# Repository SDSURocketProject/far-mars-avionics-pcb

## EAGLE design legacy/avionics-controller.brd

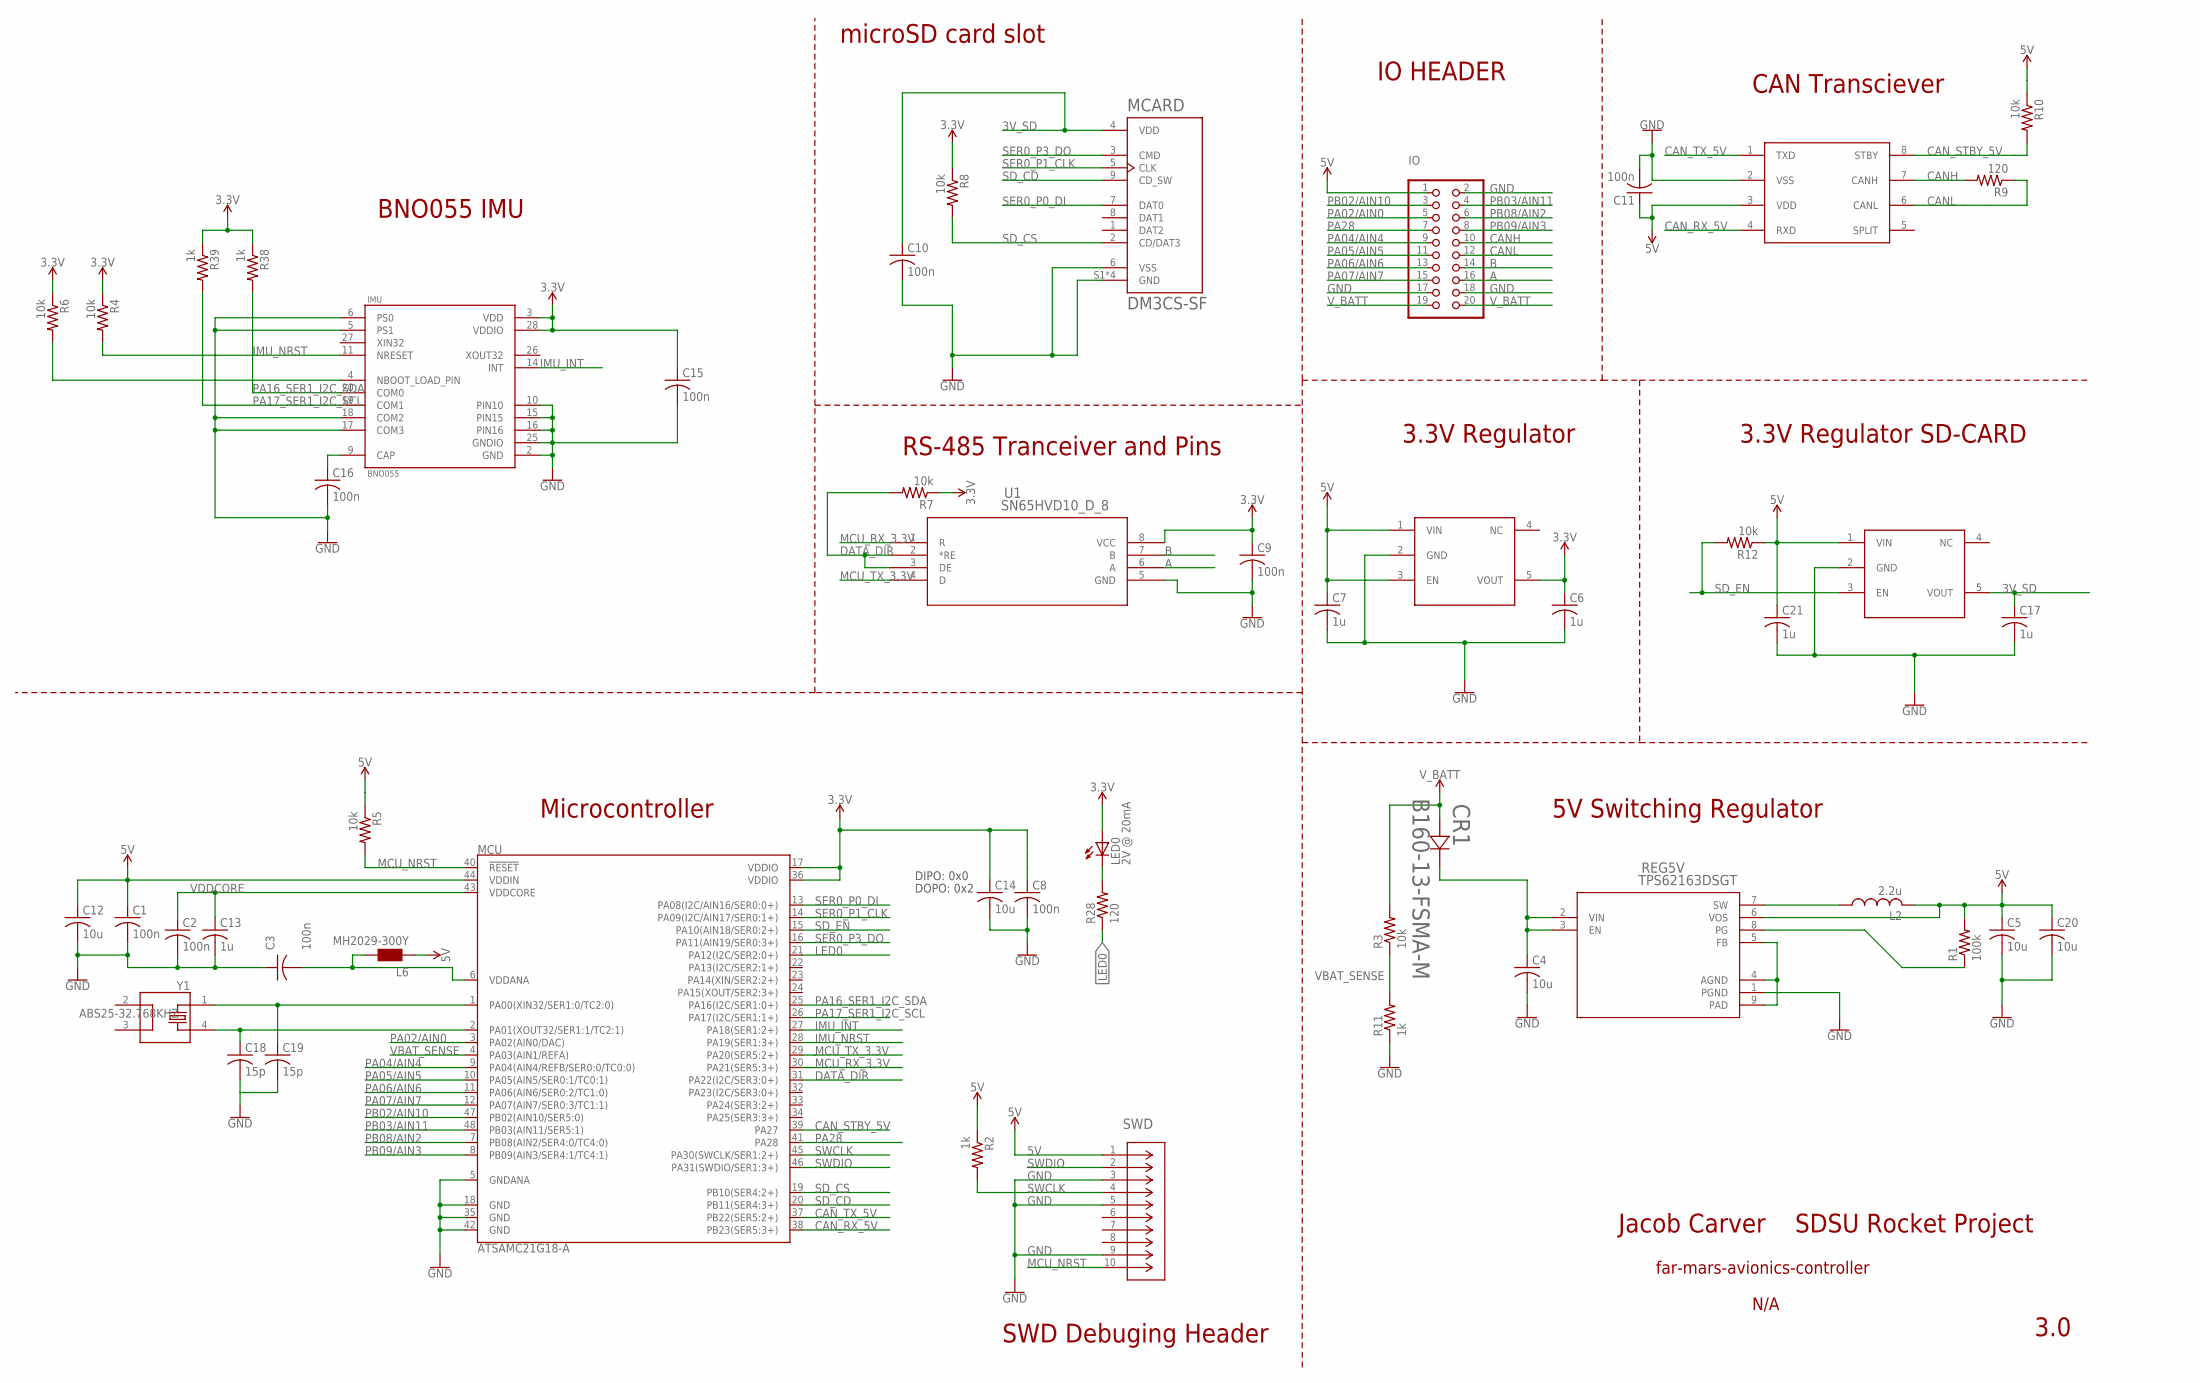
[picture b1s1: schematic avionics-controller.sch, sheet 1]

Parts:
3VREG, 3VREG-SD: 3.3VREGULATOR; SOT95P280X110-5
C1, C2, C3, C8, C9, C10, C11, C15, C16: 100n; C0402
C4, C5, C12, C14, C20: 10u; C0603
C6, C7, C13, C17, C21: 1u; C0402
C18, C19: 15p; C0402
CAN: MCP2561T-E8SOIC; SOIC127P600X175-8
CR1: B160-13-FSMA-M; SMA-M
IMU: BNO055; LGA28R50P4X10_380X520X100
IO: PINHD-2X10/90; 2X10/90
L2: 2.2u; L2012C
L6: MH2029-300Y; 0805
LED0: 2V @ 20mA; CHIPLED_0603
MCARD: DM3CS-SF; HRS_DM3CS-SF
MCU: ATSAMC21G18-A; TQFP-48
R1: 100k; R0402
R2, R11, R38, R39: 1k; R0402
R3, R4, R5, R6, R7, R8, R10, R12: 10k; R0402
R9, R28: 120; R0402
REG5V: TPS62163DSGT; DSG8_1P6X0P9
SWD: DEBUG-HEADER; CONN_MINITEK_2X5_HDR
U1: SN65HVD10_D_8; D8
Y1: ABS25-32.768KHZ; ABS25-32.768KHZ-6-T

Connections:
3.3V: 3VREG.5 (VOUT), C6.1, C8.1, C9.1, C14.1, C15.1, IMU.3 (VDD), IMU.28 (VDDIO), LED0.A, MCU.17 (VDDIO), MCU.36 (VDDIO), R4.1, R6.1, R7.1, R8.1, R38.1, R39.1, U1.8 (VCC)
3V_SD: 3VREG-SD.5 (VOUT), C10.1, C17.1, MCARD.4 (VDD)
5V: 3VREG.1 (VIN), 3VREG.3 (EN), 3VREG-SD.1 (VIN), C1.1, C5.1, C7.1, C11.1, C12.1, C20.1, C21.1, CAN.3 (VDD), IO.1, L2.2, L6.1, MCU.44 (VDDIN), R1.2, R2.1, R5.1, R10.1, R12.1, REG5V.6 (VOS), SWD.1
A: IO.16, U1.6 (A)
B: IO.14, U1.7 (B)
CANH: CAN.7 (CANH), IO.10, R9.2
CANL: CAN.6 (CANL), IO.12, R9.1
CAN_RX_5V: CAN.4 (RXD), MCU.38 (PB23(SER5:3+))
CAN_STBY_5V: CAN.8 (STBY), MCU.39 (PA27), R10.2
CAN_TX_5V: CAN.1 (TXD), MCU.37 (PB22(SER5:2+))
DATA_DIR: MCU.31 (PA22(I2C/SER3:0+)), R7.2, U1.2 (*RE), U1.3 (DE)
GND: 3VREG.2 (GND), 3VREG-SD.2 (GND), C1.2, C2.2, C3.1, C4.2, C5.2, C6.2, C7.2, C8.2, C9.2, C10.2, C11.2, C12.2, C13.2, C14.2, C15.2, C16.2, C17.2, C18.2, C19.2, C20.2, C21.2, CAN.2 (VSS), IMU.2 (GND), IMU.5 (PS1), IMU.6 (PS0), IMU.10 (PIN10), IMU.15 (PIN15), IMU.16 (PIN16), IMU.17 (COM3), IMU.18 (COM2), IMU.25 (GNDIO), IO.2, IO.17, IO.18, MCARD.6 (VSS), MCARD.S1 (GND), MCARD.S2 (GND), MCARD.S3 (GND), MCARD.S5 (GND), MCU.5 (GNDANA), MCU.18 (GND), MCU.35 (GND), MCU.42 (GND), R11.1, REG5V.1 (PGND), SWD.3, SWD.5, SWD.9, U1.5 (GND)
IMU_INT: IMU.14 (INT), MCU.27 (PA18(SER1:2+))
IMU_NRST: IMU.11 (NRESET), MCU.28 (PA19(SER1:3+)), R4.2
LED0: MCU.21 (PA12(I2C/SER2:0+)), R28.1
MCU_NRST: MCU.40 (!RESET!), R5.2, SWD.10
MCU_RX_3.3V: MCU.30 (PA21(SER5:3+)), U1.1 (R)
MCU_TX_3.3V: MCU.29 (PA20(SER5:2+)), U1.4 (D)
unnamed: R1.1, REG5V.8 (PG)
unnamed: C3.2, L6.2, MCU.6 (VDDANA)
unnamed: L2.1, REG5V.7 (SW)
unnamed: REG5V.4 (AGND), REG5V.5 (FB), REG5V.9 (PAD)
unnamed: C4.1, CR1.1 (12), REG5V.2 (VIN), REG5V.3 (EN)
unnamed: C19.1, MCU.1 (PA00(XIN32/SER1:0/TC2:0)), Y1.1
unnamed: C18.1, MCU.2 (PA01(XOUT32/SER1:1/TC2:1)), Y1.4
unnamed: C16.1, IMU.9 (CAP)
unnamed: IMU.4 (NBOOT_LOAD_PIN), R6.2
unnamed: LED0.C, R28.2
PA02/AIN0: IO.5, MCU.3 (PA02(AIN0/DAC))
PA04/AIN4: IO.9, MCU.9 (PA04(AIN4/REFB/SER0:0/TC0:0))
PA05/AIN5: IO.11, MCU.10 (PA05(AIN5/SER0:1/TC0:1))
PA06/AIN6: IO.13, MCU.11 (PA06(AIN6/SER0:2/TC1:0))
PA07/AIN7: IO.15, MCU.12 (PA07(AIN7/SER0:3/TC1:1))
PA16_SER1_I2C_SDA: IMU.20 (COM0), MCU.25 (PA16(I2C/SER1:0+)), R38.2
PA17_SER1_I2C_SCL: IMU.19 (COM1), MCU.26 (PA17(I2C/SER1:1+)), R39.2
PA28: IO.7, MCU.41 (PA28)
PB02/AIN10: IO.3, MCU.47 (PB02(AIN10/SER5:0))
PB03/AIN11: IO.4, MCU.48 (PB03(AIN11/SER5:1))
PB08/AIN2: IO.6, MCU.7 (PB08(AIN2/SER4:0/TC4:0))
PB09/AIN3: IO.8, MCU.8 (PB09(AIN3/SER4:1/TC4:1))
SD_CD: MCARD.9 (CD_SW), MCU.20 (PB11(SER4:3+))
SD_CS: MCARD.2 (CD/DAT3), MCU.19 (PB10(SER4:2+)), R8.2
SD_EN: 3VREG-SD.3 (EN), MCU.15 (PA10(AIN18/SER0:2+)), R12.2
SER0_P0_DI: MCARD.7 (DAT0), MCU.13 (PA08(I2C/AIN16/SER0:0+))
SER0_P1_CLK: MCARD.5 (CLK), MCU.14 (PA09(I2C/AIN17/SER0:1+))
SER0_P3_DO: MCARD.3 (CMD), MCU.16 (PA11(AIN19/SER0:3+))
SWCLK: MCU.45 (PA30(SWCLK/SER1:2+)), R2.2, SWD.4
SWDIO: MCU.46 (PA31(SWDIO/SER1:3+)), SWD.2
VBAT_SENSE: MCU.4 (PA03(AIN1/REFA)), R3.1, R11.2
VDDCORE: C2.1, C13.1, MCU.43 (VDDCORE)
V_BATT: CR1.2 (21), IO.19, IO.20, R3.2

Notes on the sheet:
DIPO: 0x0
DOPO: 0x2
RS-485 Tranceiver and Pins
SWD Debuging Header
microSD card slot
IO HEADER
3.3V Regulator
CAN Transciever
5V Switching Regulator
Microcontroller
BNO055 IMU
3.3V Regulator SD-CARD
3.0
Jacob Carver SDSU Rocket Project
N/A
far-mars-avionics-controller

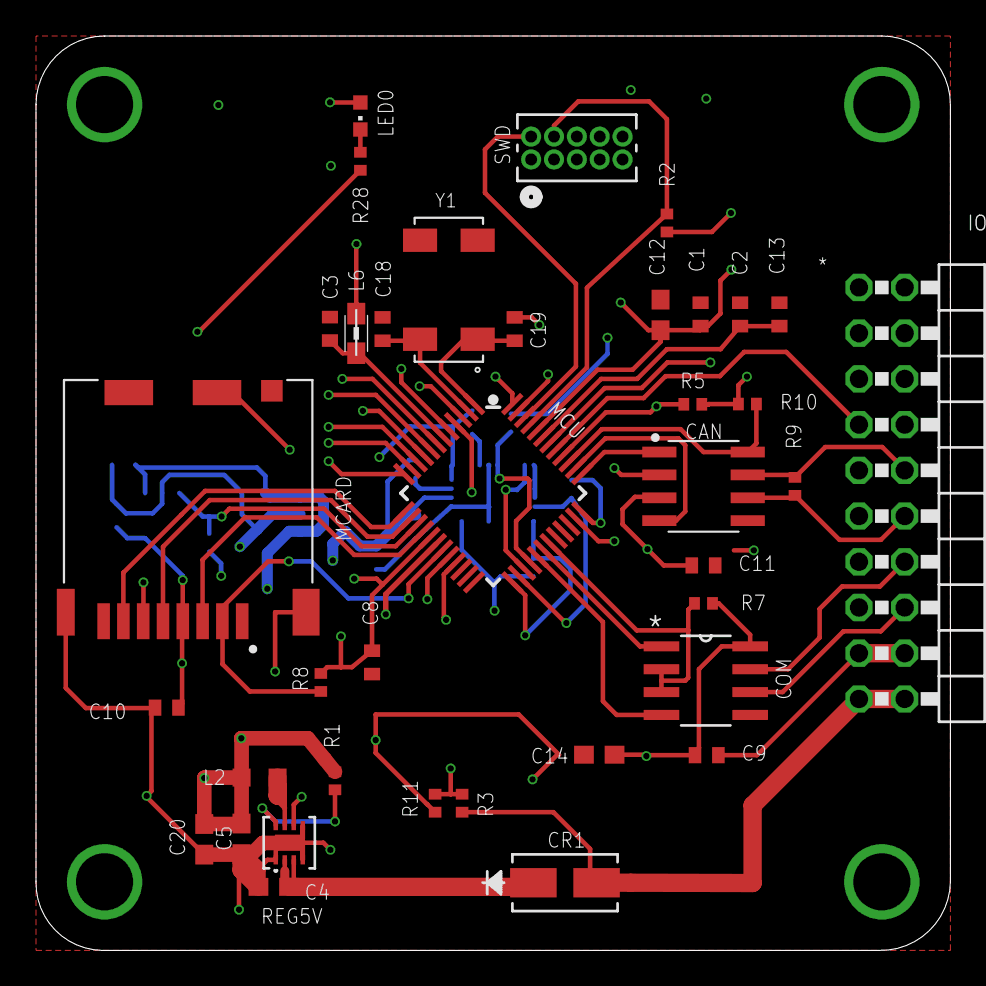
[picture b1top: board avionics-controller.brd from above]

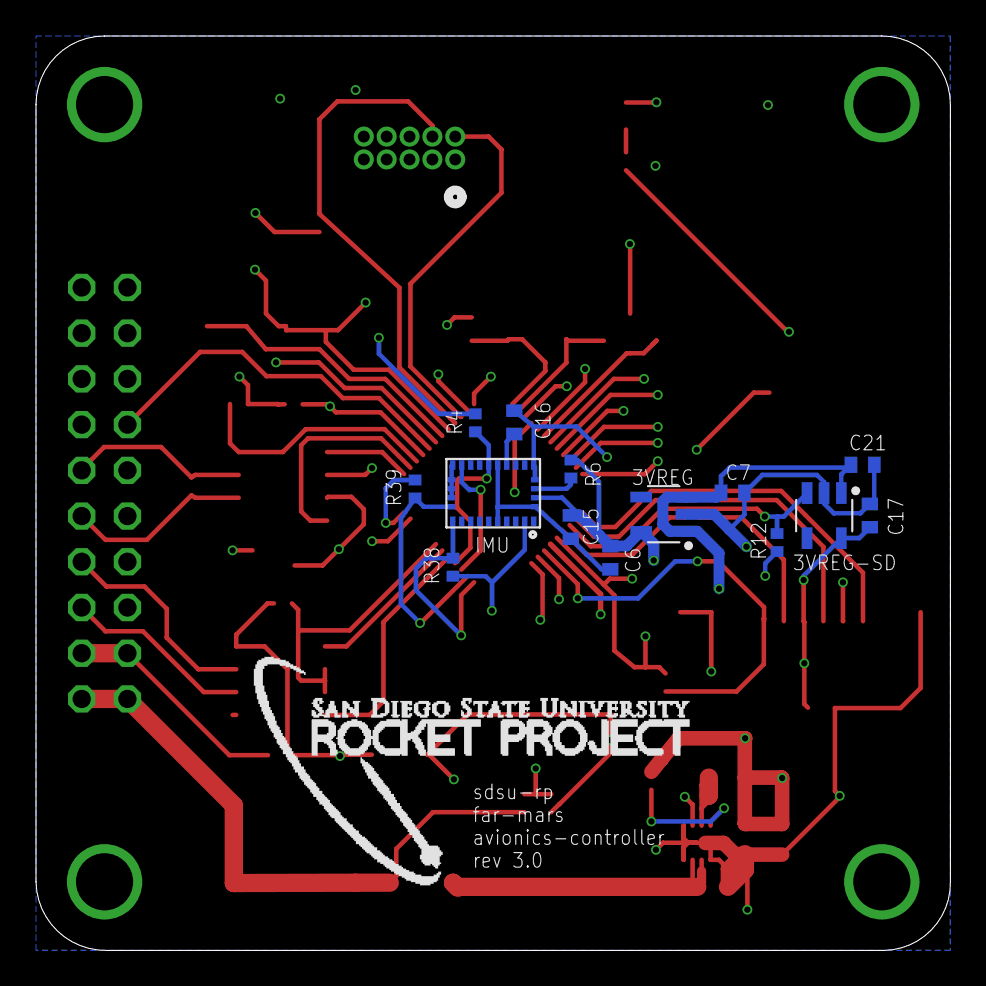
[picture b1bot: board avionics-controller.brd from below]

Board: 4 copper layers, 50.8 x 50.8 mm, 52 parts (15 on the bottom side), 51 nets.

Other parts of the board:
U$6: RP-LOGO

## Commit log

2020-07-26 moved schematic to kicad

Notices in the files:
parts and their libraries:
SparkFun-IC-Microcontroller: Licensing: Creative Commons ShareAlike 4.0 International - https://creativecommons.org/licenses/by-sa/4.0
